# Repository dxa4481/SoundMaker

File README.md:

# SoundMaker
This uses the open hardware provided by arduino to modify an arduino PCB into making a sound board

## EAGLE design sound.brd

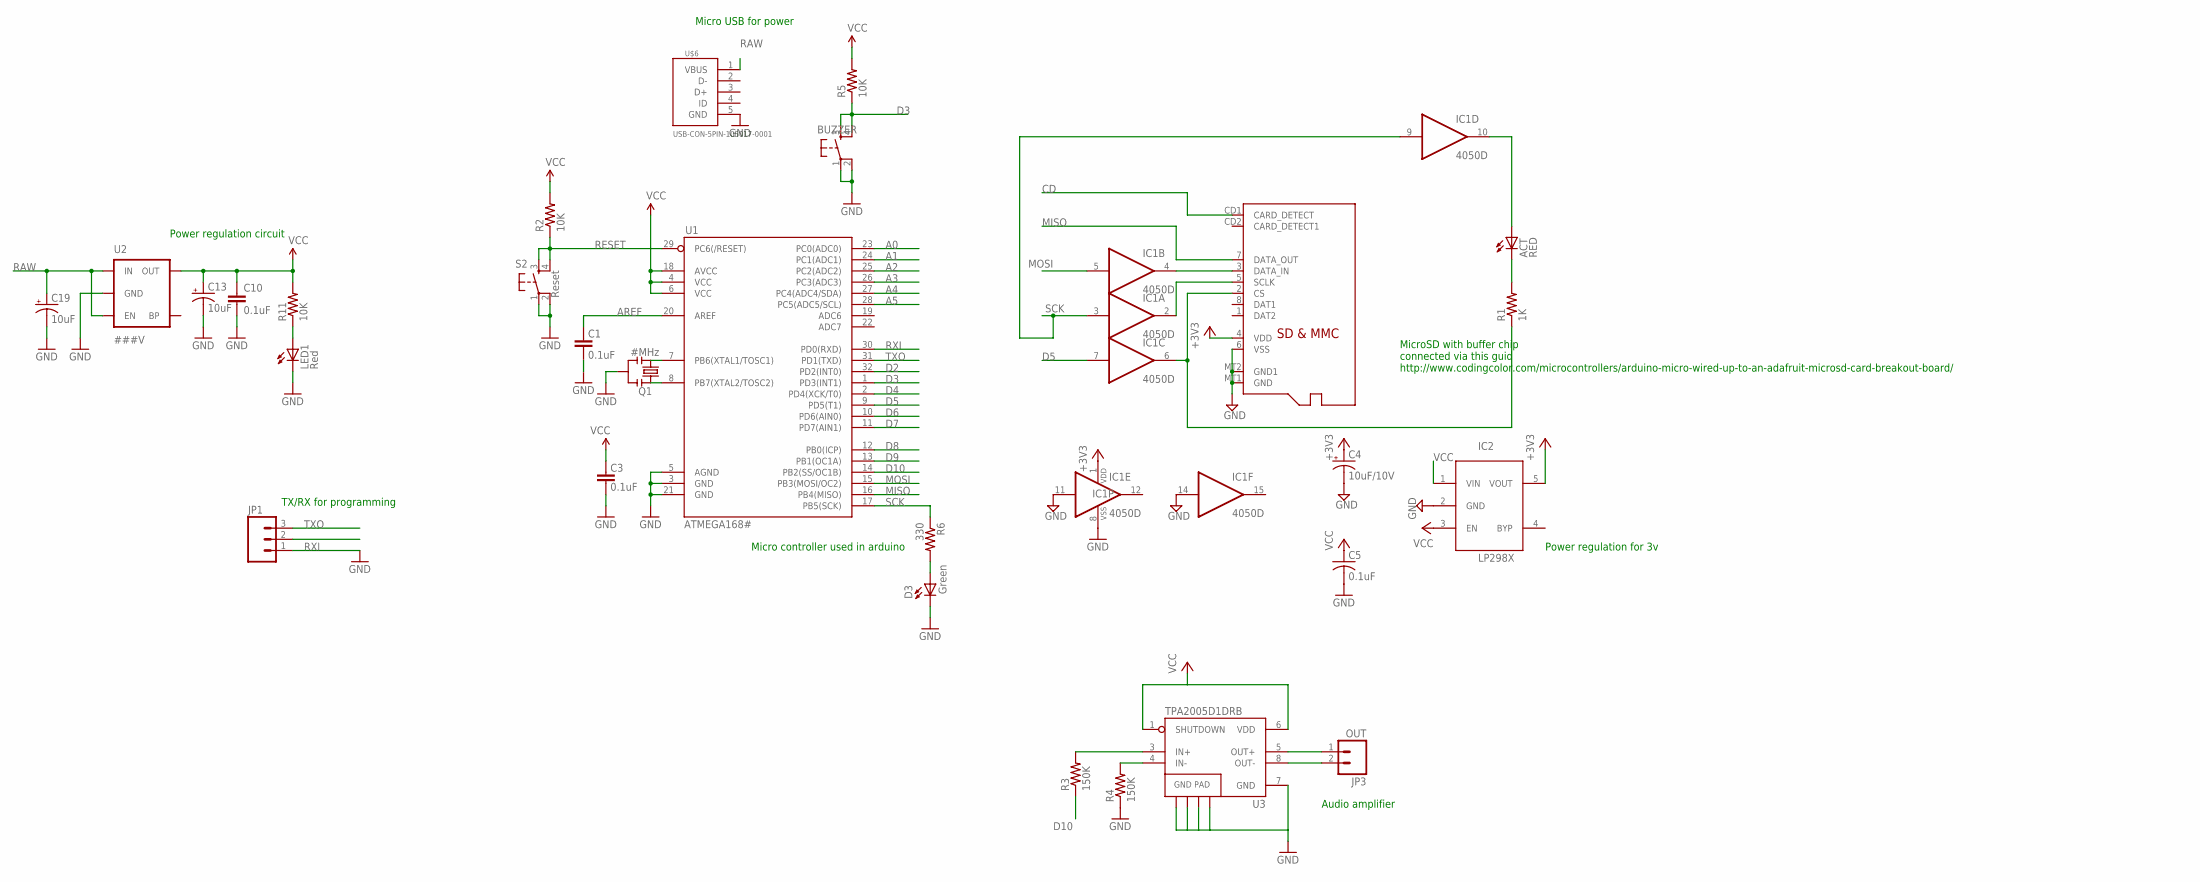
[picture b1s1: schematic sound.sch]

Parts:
ACT: RED; CHIP-LED0805
BUZZER: Reset; TACTILE_SWITCH_SMD
C1, C3, C10: 0.1uF; C0402
C4: 10uF/10V; A/3216-18R
C5: 0.1uF; C0805K
C13, C19: 10uF; EIA3216
D3: Green; LED-0603
IC1: 4050D; SO16
IC2: LP298XS; SOT23-5L
JP1: M03SMD_RA_MALE; 1X03_SMD_RA_MALE
JP3: OUT; 1X02
LED1: Red; LED-0603
Q1: #MHz; RESONATOR-SMD
R1: 1K; R0805
R2, R5, R11: 10K; C0402
R3, R4: 150K; 0603-RES
R6: 330; C0402
S2: Reset; TACTILE_SWITCH_SMD
U1: ATMEGA168#; TQFP32-08
U2: ###V; SOT23-5
U3: TPA2005D1DRB; QFN-8_PAD
U$6: USB-CON-5PIN-105017-0001; USB-MICRO-MOLEX-105017-0001
X1: MICROSD

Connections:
+3V3: C4.+, IC1.1 (VDD), IC2.5 (VOUT), X1.4 (VDD)
A0: U1.23 (PC0(ADC0))
A1: U1.24 (PC1(ADC1))
A2: U1.25 (PC2(ADC2))
A3: U1.26 (PC3(ADC3))
A4: U1.27 (PC4(ADC4/SDA))
A5: U1.28 (PC5(ADC5/SCL))
AREF: C1.2, U1.20 (AREF)
CD: X1.CD1 (CARD_DETECT)
D2: U1.32 (PD2(INT0))
D3: BUZZER.3, BUZZER.4, R5.1, U1.1 (PD3(INT1))
D4: U1.2 (PD4(XCK/T0))
D5: IC1.7 (I), U1.9 (PD5(T1))
D6: U1.10 (PD6(AIN0))
D7: U1.11 (PD7(AIN1))
D8: U1.12 (PB0(ICP))
D9: U1.13 (PB1(OC1A))
D10: R3.1, U1.14 (PB2(SS/OC1B))
GND: BUZZER.1, BUZZER.2, C1.1, C3.1, C4.-, C5.2, C10.2, C13.C (-), C19.C (-), D3.C, IC1.8 (VSS), IC1.11 (I), IC1.14 (I), IC2.2 (GND), LED1.C, Q1.2, S2.1, S2.2, U1.3 (GND), U1.5 (AGND), U1.21 (GND), U2.2 (GND), U3.7 (GND), U3.10 (GND), U3.11 (GND), U3.12 (GND), U3.13 (GND), U$6.5 (GND), X1.6 (VSS), X1.MT1 (GND), X1.MT2 (GND1)
MISO: U1.16 (PB4(MISO)), X1.7 (DATA_OUT)
MOSI: IC1.5 (I), U1.15 (PB3(MOSI/OC2))
unnamed: Q1.1, U1.8 (PB7(XTAL2/TOSC2))
unnamed: Q1.3, U1.7 (PB6(XTAL1/TOSC1))
unnamed: ACT.A, IC1.10 (O)
unnamed: IC1.2 (O), X1.5 (SCLK)
unnamed: IC1.6 (O), R1.1, X1.2 (CS)
unnamed: ACT.C, R1.2
unnamed: D3.A, R6.2
unnamed: IC1.4 (O), X1.3 (DATA_IN)
unnamed: JP3.1, U3.5 (OUT+)
unnamed: JP3.2, U3.8 (OUT-)
unnamed: R3.2, U3.3 (IN+)
unnamed: R4.2, U3.4 (IN-)
unnamed: LED1.A, R11.1
RAW: C19.A (+), U2.1 (IN), U2.3 (EN)
RESET: R2.1, S2.3, S2.4, U1.29 (PC6(/RESET))
RXI: JP1.2, U1.30 (PD0(RXD))
SCK: IC1.3 (I), IC1.9 (I), R6.1, U1.17 (PB5(SCK))
TXO: JP1.3, U1.31 (PD1(TXD))
VBUS: U$6.1 (VBUS)
VCC: C3.2, C5.1, C10.1, C13.A (+), IC2.1 (VIN), IC2.3 (EN), R2.2, R5.2, R11.2, U1.4 (VCC), U1.6 (VCC), U1.18 (AVCC), U2.5 (OUT), U3.1 (SHUTDOWN), U3.6 (VDD)

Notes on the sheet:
TX/RX for programming
Micro controller used in arduino
Power regulation circuit
Micro USB for power
MicroSD with buffer chip connected via this guid http://www.codingcolor.com/microcontrollers/arduino-micro-wired-up-to-an-adafruit-microsd-card-breakout-board/
Audio amplifier
Power regulation for 3v

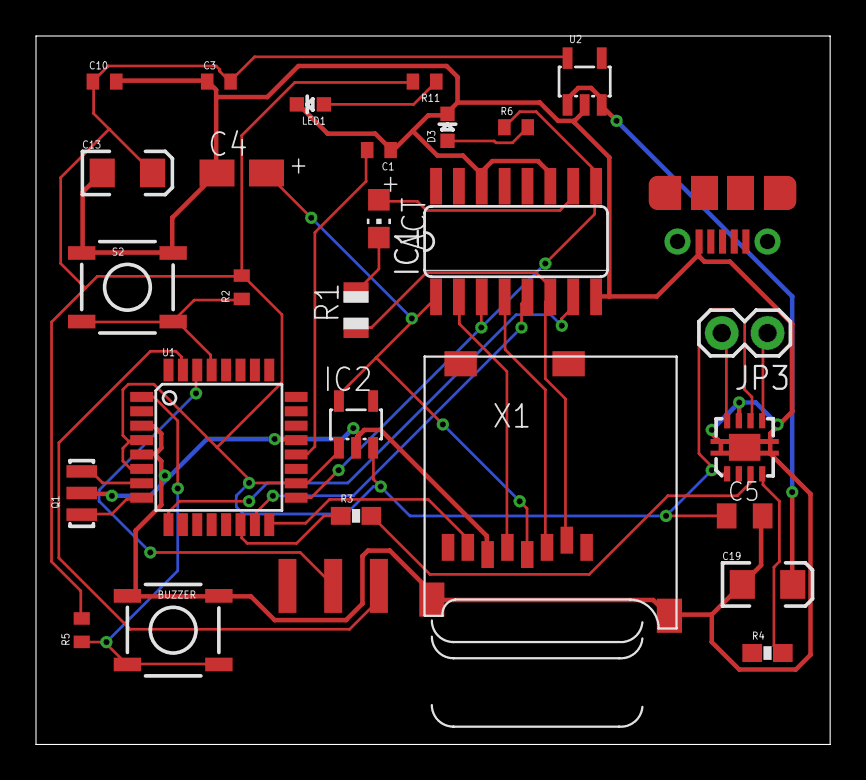
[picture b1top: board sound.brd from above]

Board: 2 copper layers, 44.1 x 39.4 mm, 29 parts (0 on the bottom side), 27 nets.

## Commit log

2015-02-21 initial commit, includes rough schematic and board file

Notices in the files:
parts and their libraries:
SparkFun-Connectors: Licensing: Creative Commons ShareAlike 4.0 International - https://creativecommons.org/licenses/by-sa/4.0
